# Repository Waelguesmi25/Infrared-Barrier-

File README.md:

# 🌐 Infrared Barrier Project  

## 📌 Overview  
This repository contains the design files for an **Infrared Barrier system** that detects interruptions in an infrared beam and processes them for counting or triggering events.  
The project was developed for educational purposes, focusing on a compact and adaptable design.  

## ✨ Features  
* Detects objects passing through an infrared beam.  
* Counts and displays events in real time.  
* Visual and/or audible indicators for detections.  
* Adjustable timing and sensitivity.  
* PCB layout and schematic ready for fabrication.  

## 📂 Repository Contents  
* **barriere_IR.sch** – Schematic file (circuit design).  
* **barriere_IR.brd** – PCB layout file (board design).  
* **schéma_de_routage.pdf** – Routing diagram.  
* **schéma_d'implantation.pdf** – Component placement diagram.  
* **TYPON.pdf** – PCB mask for manufacturing or DIY etching.  
* **barriere_IR.s## / barriere_IR.s#1** – Backup schematic versions.  

## 🛠 Usage  
1. **Open & Edit** → Use *Autodesk Eagle* to view or modify the schematic and PCB files.  
2. **Fabricate PCB** → Generate Gerber files or use the provided PDF mask for DIY etching.  
3. **Assemble** → Follow the placement diagram for soldering components.  
4. **Test & Calibrate** → Power the system, test beam interruption detection, and adjust sensitivity if needed.  

## 📜 License  
*Open-source under the **MIT License*** – free to use, modify, and adapt for personal or educational purposes.  

**👤 Author:** *Wael Guesmi*

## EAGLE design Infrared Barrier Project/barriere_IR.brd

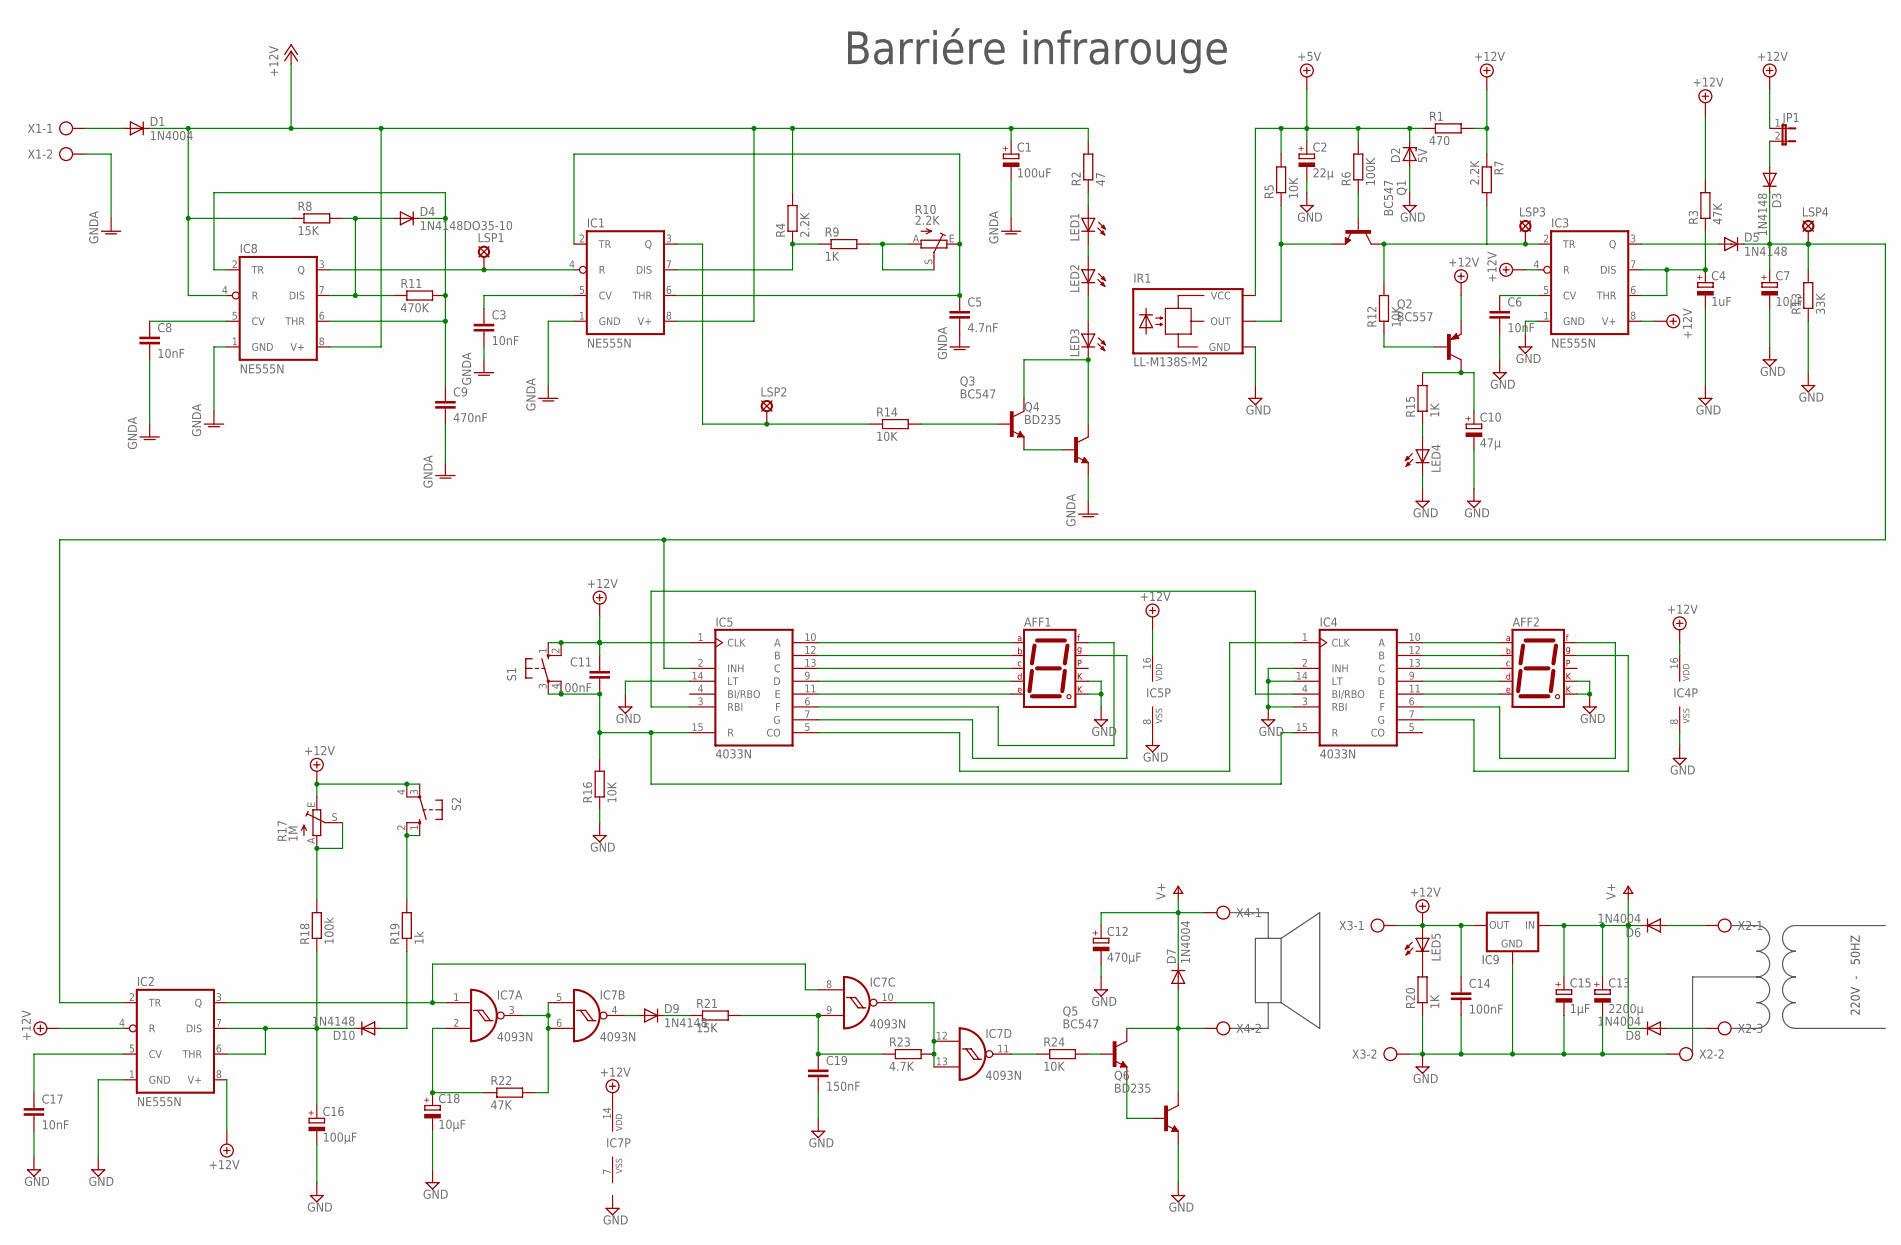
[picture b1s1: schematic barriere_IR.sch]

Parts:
AFF1, AFF2: 7SEG-CK; 7SEG-13
C1: 100uF; E5-10,5
C2: 22µ; E2,5-5
C3, C6, C8, C17: 10nF; C050-035X075
C4: 1uF; E2,5-5
C5: 4.7nF; C050-035X075
C7, C18: 10µF; E2,5-5
C9: 470nF; C102-043X133
C10: 47µ; E2,5-5
C11: 100nF; C050-035X075
C12: 470µF; E5-10,5
C13: 2200µ; E5-13
C14: 100nF; C050-030X075
C15: 1µF; E2,5-5
C16: 100µF; E5-10,5
C19: 150nF; C050-035X075
D1, D6, D7, D8: 1N4004; DO41-10
D2: 5V; DO34Z7
D3, D5, D9, D10: 1N4148; DO35-10
D4: 1N4148DO35-10; DO35-10
IC1, IC2, IC3, IC8: NE555N; DIL08
IC4, IC5: 4033N; DIL16
IC7: 4093N; DIL14
IC9: 78XXS
IR1: LL-M138S-M2
JP1: JP1E; JP1
LED1, LED2, LED3, LED4, LED5: LED5MM
LSP1, LSP2, LSP3, LSP4: LSP10
Q1, Q3, Q5: BC547; TO92
Q2: BC557; TO92
Q4, Q6: BD235; TO126
R1: 470; 0207/10
R2: 47; 0207/10
R3, R22: 47K; 0207/10
R4, R7: 2.2K; 0207/10
R5, R12, R14, R16, R24: 10K; 0207/10
R6: 100K; 0207/10
R8, R21: 15K; 0207/10
R9, R15, R20: 1K; 0207/10
R10: 2.2K; CA9V
R11: 470K; 0207/10
R13: 33K; 0207/10
R17: 1M; CA9V
R18: 100k; 0207/10
R19: 1k; 0207/10
R23: 4.7K; 0207/10
S1, S2: 10-XX; B3F-10XX
X1, X3, X4: AK300/2
X2: AK300/3

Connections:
+5V: C2.+, D2.C, IR1.3 (VCC), R1.1, R5.2, R6.2
+12V: C11.1, C14.1, IC2.4 (R), IC2.8 (V+), IC3.4 (R), IC3.8 (V+), IC4.16 (VDD), IC5.1 (CLK), IC5.16 (VDD), IC7.14 (VDD), IC9.OUT, JP1.1, LED5.A, Q2.1 (E), R1.2, R3.2, R7.1, R17.E, S1.1 (S), S1.2 (S1), S2.3, S2.4 (P1), X3.1
+12V/1: C1.+, D1.C, IC1.8 (V+), IC8.4 (R), IC8.8 (V+), R2.2, R4.2, R8.1
GND: AFF1.3 (CK1), AFF1.8 (CK2), AFF2.3 (CK1), AFF2.8 (CK2), C2.-, C4.-, C6.2, C7.-, C10.-, C12.-, C13.-, C14.2, C15.-, C16.-, C17.2, C18.-, C19.2, D2.A, IC2.1 (GND), IC3.1 (GND), IC4.2 (INH), IC4.3 (RBI), IC4.8 (VSS), IC4.14 (LT), IC5.8 (VSS), IC5.14 (LT), IC9.GND, IR1.2 (GND), LED4.K (C), Q6.1 (E), R13.1, R16.1, R20.1, X2.2, X3.2
GNDA: C1.-, C3.2, C5.2, C8.2, C9.2, IC1.1 (GND), IC8.1 (GND), Q4.1 (E), X1.2
unnamed: D1.A, X1.1
unnamed: D4.A, IC8.7 (DIS), R8.2, R11.1
unnamed: IC1.3 (Q), LSP2.MP, R14.1
unnamed: C9.1, D4.C, IC8.2 (TR), IC8.6 (THR), R11.2
unnamed: IC1.4 (R), IC8.3 (Q), LSP1.MP
unnamed: C3.1, IC1.5 (CV)
unnamed: IC1.7 (DIS), R4.1, R9.1
unnamed: C8.1, IC8.5 (CV)
unnamed: R9.2, R10.A, R10.S
unnamed: IR1.1 (OUT), Q1.1 (E), R5.1
unnamed: C5.1, IC1.2 (TR), IC1.6 (THR), R10.E
unnamed: C6.1, IC3.5 (CV)
unnamed: LED1.A, R2.1
unnamed: LED1.K (C), LED2.A
unnamed: LED2.K (C), LED3.A
unnamed: LED3.K (C), Q3.3 (C), Q4.2 (C)
unnamed: Q3.1 (E), Q4.3 (B)
unnamed: Q3.2 (B), R14.2
unnamed: C4.+, IC3.6 (THR), IC3.7 (DIS), R3.1
unnamed: D5.A, IC3.3 (Q)
unnamed: IC3.2 (TR), LSP3.MP, Q1.3 (C), R7.2, R12.2
unnamed: Q1.2 (B), R6.1
unnamed: C7.+, D3.C, D5.C, IC2.2 (TR), IC5.2 (INH), LSP4.MP, R13.2
unnamed: D3.A, JP1.2
unnamed: Q2.2 (B), R12.1
unnamed: C10.+, Q2.3 (C), R15.2
unnamed: C11.2, IC4.15 (R), IC5.15 (R), R16.2, S1.3, S1.4 (P1)
unnamed: LED4.A, R15.1
unnamed: AFF1.7 (A), IC5.10 (A)
unnamed: AFF1.6 (B), IC5.12 (B)
unnamed: AFF1.4 (C), IC5.13 (C)
unnamed: AFF1.2 (D), IC5.9 (D)
unnamed: AFF1.1 (E), IC5.11 (E)
unnamed: AFF1.9 (F), IC5.6 (F)
unnamed: AFF1.10 (G), IC5.7 (G)
unnamed: IC4.1 (CLK), IC5.5 (CO)
unnamed: C17.1, IC2.5 (CV)
unnamed: AFF2.7 (A), IC4.10 (A)
unnamed: IC4.4 (BI/RBO), IC5.3 (RBI)
unnamed: AFF2.6 (B), IC4.12 (B)
unnamed: AFF2.4 (C), IC4.13 (C)
unnamed: AFF2.2 (D), IC4.9 (D)
unnamed: AFF2.1 (E), IC4.11 (E)
unnamed: AFF2.9 (F), IC4.6 (F)
unnamed: AFF2.10 (G), IC4.7 (G)
unnamed: C16.+, D10.C, IC2.6 (THR), IC2.7 (DIS), R18.1
unnamed: R19.2, S2.1 (S), S2.2 (S1)
unnamed: R17.A, R17.S, R18.2
unnamed: D10.A, R19.1
unnamed: C18.+, IC7.2 (I1), R22.1
unnamed: IC2.3 (Q), IC7.1 (I0), IC7.8 (I0)
unnamed: IC7.3 (O), IC7.5 (I0), IC7.6 (I1), R22.2
unnamed: D9.A, IC7.4 (O)
unnamed: D9.C, R21.1
unnamed: C19.1, IC7.9 (I1), R21.2, R23.1
unnamed: IC7.10 (O), IC7.12 (I0), IC7.13 (I1), R23.2
unnamed: IC7.11 (O), R24.1
unnamed: Q5.2 (B), R24.2
unnamed: Q5.1 (E), Q6.3 (B)
unnamed: D7.A, Q5.3 (C), Q6.2 (C), X4.2
unnamed: LED5.K (C), R20.2
unnamed: D8.A, X2.3
unnamed: D6.A, X2.1
V+: C12.+, C13.+, C15.+, D6.C, D7.C, D8.C, IC9.IN, X4.1
VSS: IC7.7 (VSS)

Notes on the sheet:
220V - 50HZ
Barriére infrarouge

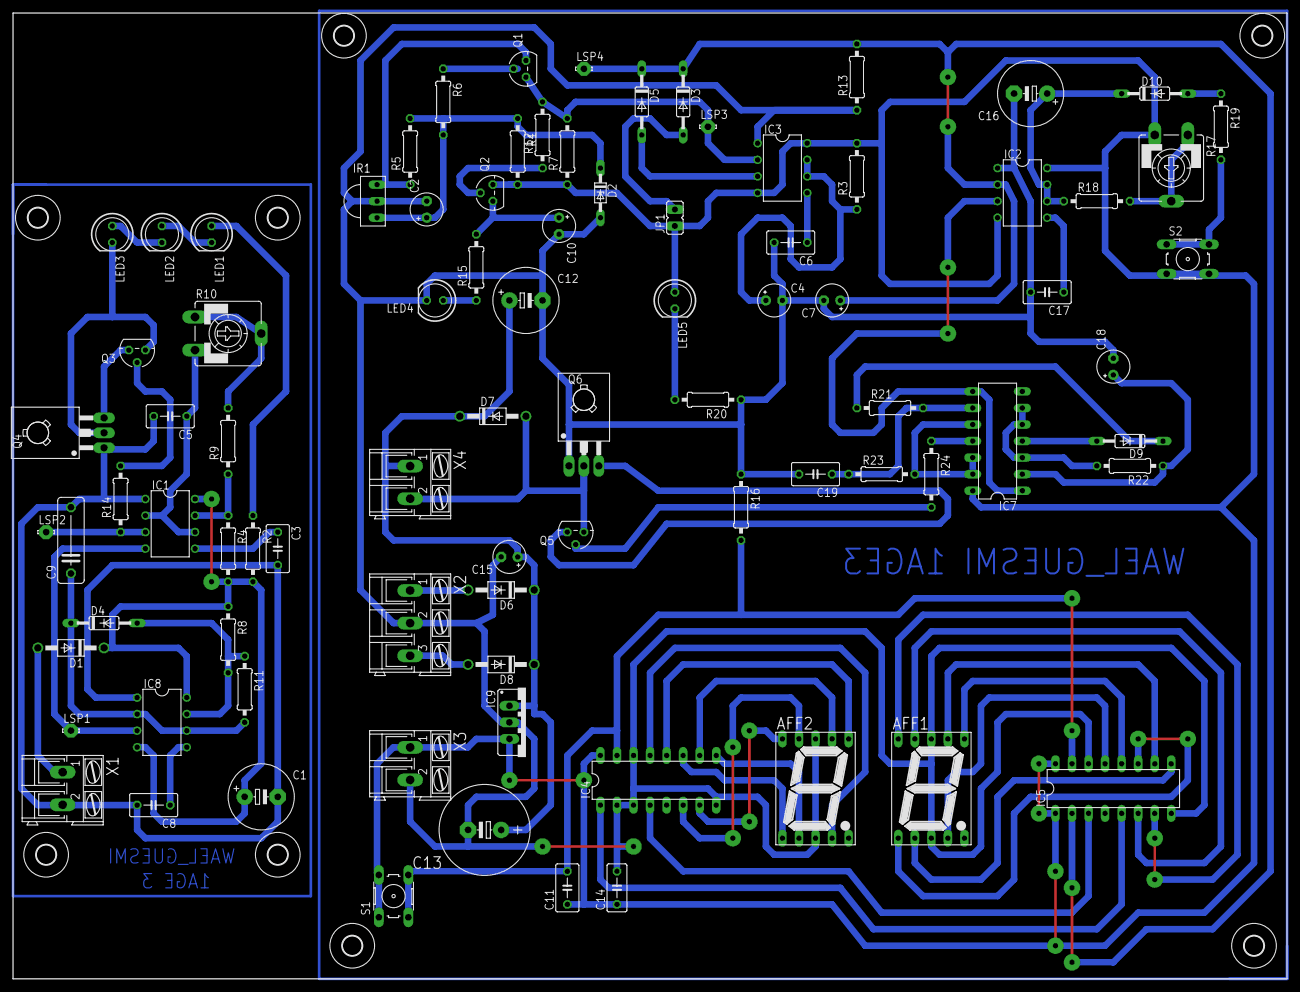
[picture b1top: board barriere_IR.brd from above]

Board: 2 copper layers, 195.6 x 148.3 mm, 94 parts (0 on the bottom side), 69 nets.

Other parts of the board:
U$1, U$2, U$3, U$4, U$5, U$6, U$7, U$8: 3,0

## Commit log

2025-08-12 IMPORTANT
2025-08-12 README.md
